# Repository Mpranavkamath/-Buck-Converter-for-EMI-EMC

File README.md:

# -Buck-Converter-for-EMI-EMC
A 12V to 5V buck converter with a custom current-sensing stage and firmware-controlled spread-spectrum PWM, built to study how switching frequency spreading changes conducted EMI.

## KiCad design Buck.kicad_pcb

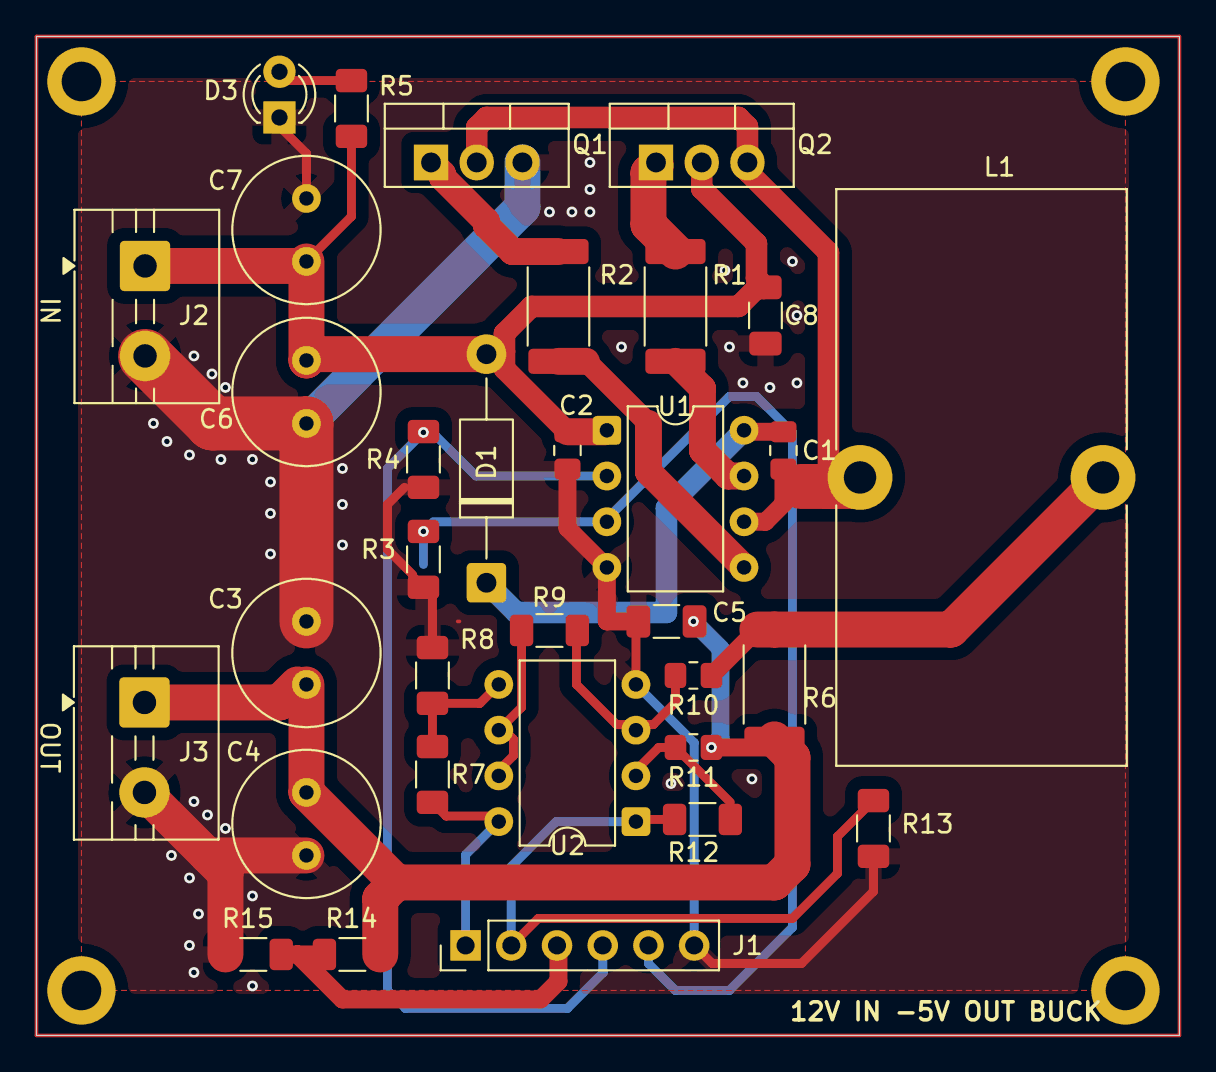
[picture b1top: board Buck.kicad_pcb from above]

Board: 2 copper layers, 63.5 x 55.5 mm, 35 parts (0 on the bottom side), 20 nets.

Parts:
C1, C2: 1uF; C_0805_2012Metric_Pad1.18x1.45mm_HandSolder
C3, C4, C6, C7: 47uF; C_Radial_D8.0mm_H11.5mm_P3.50mm
C5: 10uF; C_1206_3216Metric_Pad1.33x1.80mm_HandSolder
C8: 1uF; C_1206_3216Metric_Pad1.33x1.80mm_HandSolder
D1: 1N5819; D_DO-41_SOD81_P12.70mm_Horizontal
D3: LED; LED_D3.0mm
GND REF: MountingHole_2.2mm_M2_DIN965_Pad
J1: Conn_01x05; PinHeader_1x06_P2.54mm_Vertical
J2: Input; TerminalBlock_MaiXu_MX126-5.0-02P_1x02_P5.00mm
J3: Out; TerminalBlock_MaiXu_MX126-5.0-02P_1x02_P5.00mm
L1: 120uH; L_Toroid_Vertical_L31.8mm_W15.9mm_P13.50mm_Bourns_5700
Q1, Q2: IRLB8748PbF; TO-220-3_Vertical
R1, R2: 10R; R_2512_6332Metric_Pad1.40x3.35mm_HandSolder
R3, R4, R5, R14, R15: 10k; R_1206_3216Metric_Pad1.30x1.75mm_HandSolder
R6: 50m; R_2512_6332Metric_Pad1.40x3.35mm_HandSolder
R7, R8, R9, R12: 1.5k; R_1206_3216Metric_Pad1.30x1.75mm_HandSolder
R10, R11: 300; R_0805_2012Metric_Pad1.20x1.40mm_HandSolder
R13: 1.5K; R_1206_3216Metric_Pad1.30x1.75mm_HandSolder
REF_GND: MountingHole_2.2mm_M2_DIN965_Pad
U1: IR2104; DIP-8_W7.62mm
U2: LM358; DIP-8_W7.62mm

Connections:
3V3: J1.1, R7.1, U2.8 (Vdd)
/Synchronous Buck/D: C2.1, C6.1, C7.1, C8.1, D1.2 (A), J2.1, Q2.2 (D), R5.1, U1.1 (VCC)
/Synchronous Buck/IN(HO,~LO): J1.4, R4.1, U1.2 (IN)
/Synchronous Buck/S: C1.2, L1.1, Q1.2 (D), Q2.3 (S), U1.6 (VS)
/Synchronous Buck/~SD: J1.5, R3.1, U1.3 (~SD)
Current_Amplifier_out: J1.2, R12.2, R13.1, U2.1
GND: C2.2, C3.2, C4.2, C5.2, C6.2, C7.2, C8.2, D3.1 (K), J1.6, J2.2, J3.2, Q1.3 (S), R3.2, R4.2, R8.2, R13.2, R15.2, U1.4 (COM), U2.4 (GND)
unnamed: C1.1, D1.1 (K), U1.8 (VB)
unnamed: D3.2 (A), R5.2
unnamed: Q1.1 (G), R2.2
unnamed: Q2.1 (G), R1.2
unnamed: R1.1, U1.7 (HO)
unnamed: R2.1, U1.5 (LO)
unnamed: R9.2, R10.2, U2.3 (+)
unnamed: R11.2, R12.1, U2.2 (-)
unnamed: R7.2, R8.1, U2.5 (+)
Rshunt_IN+: L1.2, R6.1, R10.1
Rshunt_IN-: C3.1, C4.1, C5.1, J3.1, R6.2, R11.1, R14.1
V_meas: J1.3, R14.2, R15.1
Vref: R9.1, U2.6 (-), U2.7
